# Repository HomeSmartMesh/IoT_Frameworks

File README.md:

# [website with overview, tutorials, mind maps,...](https://www.homesmartmesh.com/)

# [More recent github for Raspberry Pi scripts and nRF52](https://github.com/nRFMesh/nRF52_Mesh)

# Status
This repo is no longer in active maintenance, its main topics are :
* raspberry pi scripts and services, moved to the [nRF52](https://github.com/nRFMesh/nRF52_Mesh) repo
* microcontrolled based firmware
  * Low power STM8 replaced by off the shelf nRF51 and custom [nRF52](https://github.com/nRFMesh/nRF52_Mesh)
  * Power connected STM32 replaced by [ESP32_iot](https://github.com/HomeSmartMesh/esp32_iot)

# Hardware
### Wireless Sensor Tag
  * HW: [STM8 IoT Boards](https://github.com/HomeSmartMesh/STM8_IoT_Boards)
  * Firmware: [IoT STM8 ](https://github.com/HomeSmartMesh/IoT_STM8/tree/master/firmware_rf_sensors_node)
  * 8 bit Ultra low power & ultralow cost STM8L
  * BME280 (Pressure, Temperature, Humidity), MAX44009 (Ambient Light) and Magnetic switches
  * Custom RF protocol for efficiency and simplicity of the sensors usecase

### STM32 IoT Dongle
  * based on the STM32 bluepill
  * HW: Breadboard for easier RF and sensors modules integration [STM32 IoT Boards](https://github.com/wassfila/STM32_IoT_Boards)
  * Firmware: [stm32_rf_dongle subdirectory](https://github.com/HomeSmartMesh/IoT_Frameworks/tree/master/stm32_rf_dongle)
  * RF Mesh repeater: (decrement time to live, recalculate new CRC)
  * Light intensity, color sensor, proximity and gesture (APDS9960)
  * RGB status (WS2812B)

# Software running on the Raspberry pi

### C++ RF Gateway
[submodule rf_gateway](https://github.com/HomeSmartMesh/rf_gateway)
- Serial port line buffer
- Line parsing and sensor data extraction
- Adjustment of BME280 measures with provided calibration
- Publishing to the MQTT broquer

### Python Database proxies
scripts in the [submodule py_db_proxy](https://github.com/HomeSmartMesh/py_db_proxy)
- influx client
- mongo client
- json config and loggging

### React D3js webapp
[submodule web_react](https://github.com/HomeSmartMesh/web_react)
current status :
* automatic nodes config retriaval 
* automatic dashboard construction (but still in text mode)
* d3js still in a separate project, options beeing evaluated (nvd3 and vegas)

### Configuration
Configuration for the following software is available in the [config subdirectory](https://github.com/HomeSmartMesh/IoT_Frameworks/tree/master/config)

 * Mosquitto : MQTT Broquer
 * OpenHAB2 : used only for Wemo switch and other connected devices
 * Node-red : High level sensor to action configuration
 * Influxdb : time series database
 * Mongodb : complex documents database
 * Grafana : dashboard for measurements exploration
 * React+d3js : customised webapp

## Startup Launch on the Raspberry pi
to enable once
```
sudo systemctl enable openhab2
sudo systemctl enable influxdb
```

Others require manual startup added in
```
sudo nano /etc/rc.local
```
Debugging the rc.local log with adding the following lines
```
exec 2> /home/pi/share/rc.local.log   # send stderr from rc.local to a log file
exec 1>&2                             # send stdout to the same log file
set -x                                # tell sh to display commands before execution
```

```bash
#grafana
sudo systemctl start grafana-server.service
#iot_db
/home/pi/IoT_Frameworks/raspi_mesh_server/iot_db/iot_db &
#rf_gateway
sleep 2 && /home/pi/IoT_Frameworks/raspi_mesh_server/rf_gateway/gateway &
#mongodb : for some reason, mongodb service do not attempt reconnection on startup, but works when started a bit later
sleep 15 && sudo systemctl start mongodb.service
#mqtt_mongo
sleep 5 && python /home/pi/IoT_Frameworks/raspi_mesh_server/py_db_proxy/mqtt_mongo.py &
sleep 1 && python /home/pi/IoT_Frameworks/raspi_mesh_server/py_net_gateway/wemo_client.py &
sleep 5 && python /home/pi/IoT_Frameworks/raspi_mesh_server/py_net_gateway/milight_gateway.py &

```

Another example

```
/home/pi/IoT_Frameworks/raspi_mesh_server/rf_gateway/gateway &

python /home/pi/IoT_Frameworks/raspi_mesh_server/py_net_gateway/wemo_client.py &

python /home/pi/IoT_Frameworks/raspi_mesh_server/py_net_gateway/milight_gateway.py &

python /home/pi/IoT_Frameworks/raspi_mesh_server/ruler/ruler.py &

python /home/pi/IoT_Frameworks/raspi_mesh_server/py_net_gateway/raspi_status.py &

sleep 15 && python /home/pi/IoT_Frameworks/raspi_mesh_server/py_db_proxy/influx_client.py &
```

### Protocol helper
0x05 : Alive
0x07 : light
0x0A : bme280

0x06 : 6 - Living room
0x0F : 15- Workplace
0x1A : 26- Sleeping room
0x1D : 29
0x26 : 38- Rep test

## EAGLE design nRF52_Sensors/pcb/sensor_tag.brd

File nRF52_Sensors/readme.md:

# nRF52 Sensor Tag
* Soc : nRF52832 QF AA
* BME280
* APDS9960

# Board PIO connections
* SCL       : P0_29
* SDA       : P0_30
* APDS_Int  : P0_31
* UART_Tx   : P0_06

# Prerequisites
* GNU Tools ARM Embedded version : 6 2017-q2-update

# Included dependencies
* nRF SDK 15.0.0_a53641a linked as a submodule and stripped down to the required content
* nRF SDK size reduced to ~ 2.8 MB instead of the original 693 MB and can thus easily be treated as an always loaded submodule

# uart
* main.c        : uart_init() -> APP_UART_FIFO_INIT(), app_uart_put(), app_uart_get()
* app_uart.h    : APP_UART_FIFO_INIT() -> app_uart_init()
* app_uart.c    : app_uart_init() -> nrf_drv_uart_init() "legacy\nrf_drv_uart.c"
* nrf_serial.c  : nrf_serial_init(),nrf_serial_write(),nrf_serial_read()
                  nrf_serial_init() -> nrf_drv_uart_init() "legacy\nrf_drv_uart.c"

# nrf logger module
* http://infocenter.nordicsemi.com/index.jsp?topic=%2Fcom.nordic.infocenter.sdk5.v15.0.0%2Fgroup__nrf__log.html&cp=4_0_0_6_11_16
## sdk config
* NRF_LOG + NRF_LOG_BACKEND_UART_XXX
* NRFX_UARTE_ENABLED 1, NRFX_UARTE0_ENABLED 0
* NRFX_UART_ENABLED 1, NRFX_UART0_ENABLED 0
* UART_ENABLED 1
* NRFX_PRS_ENABLED 1, NRFX_PRS_BOX_4_ENABLED 1
## user macros
* NRF_LOG_INSTANCE_REGISTER()
* NRF_LOG_INFO("Hi\r\n");   
* NRF_LOG_FLUSH(); must be called if not deferred
* timestamp only when using app_timer.h

# Tools

## Python jlink wrapper
* https://github.com/square/pylink
* http://pylink.readthedocs.io/en/latest/pylink.html
* have to be used with a 32 bit python version

## sdk_config GUI
```make conf```
* http://helmpcb.com/software/cmsis-configuration-wizard

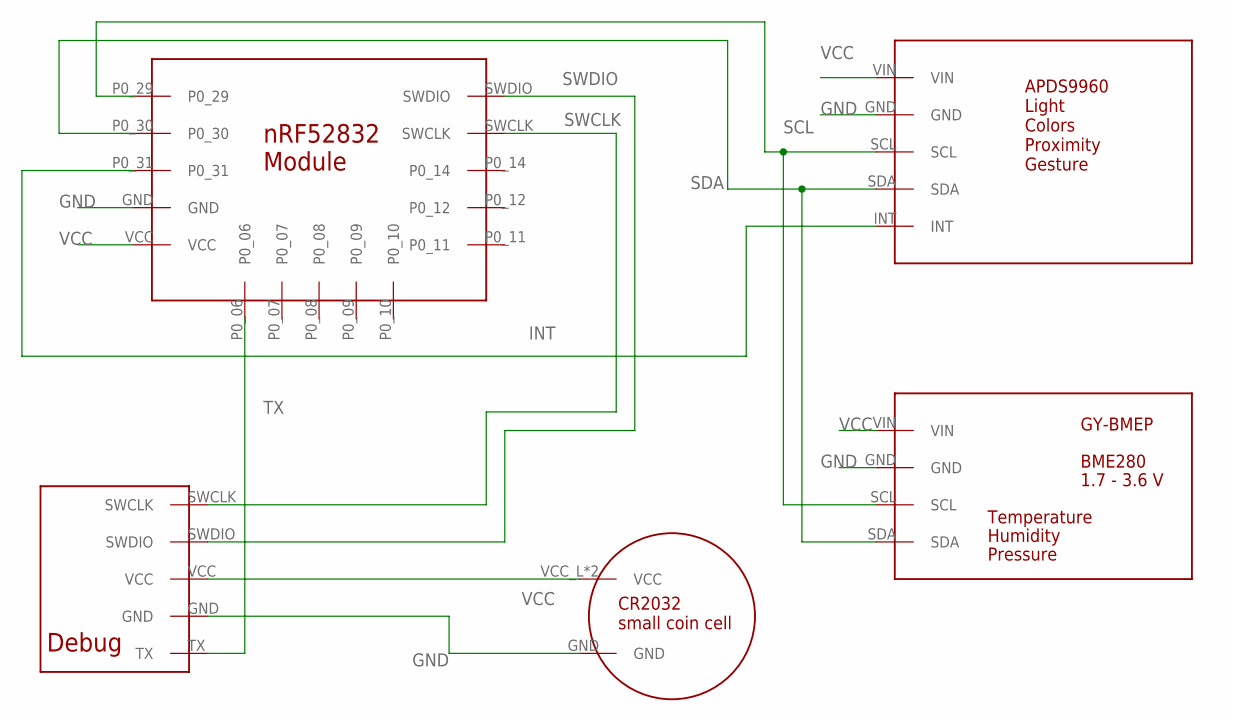
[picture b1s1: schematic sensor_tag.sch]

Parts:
U$1: GY-BMEPGY-BMEP-NOHOLE; GY-BMEP-NOHOLE
U$2: APDS9960_MODULEAPDS9960-FULL; APDS9960-FULL
U$3: NRF52832_MODULENRF52832_MOD_SMALL; NRF52832_MOD_SMALL
U$4: CR2032; CR2032_SMD
U$5: NRF_TAG_DEBUG

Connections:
GND: U$1.GND, U$2.GND, U$3.GND, U$4.GND, U$5.GND
INT: U$2.INT, U$3.P0_31
SCL: U$1.SCL, U$2.SCL, U$3.P0_29
SDA: U$1.SDA, U$2.SDA, U$3.P0_30
SWCLK: U$3.SWCLK, U$5.SWCLK
SWDIO: U$3.SWDIO, U$5.SWDIO
TX: U$3.P0_06, U$5.TX
VCC: U$1.VIN, U$2.VIN, U$3.VCC, U$4.VCC_L (VCC), U$4.VCC_R (VCC), U$5.VCC

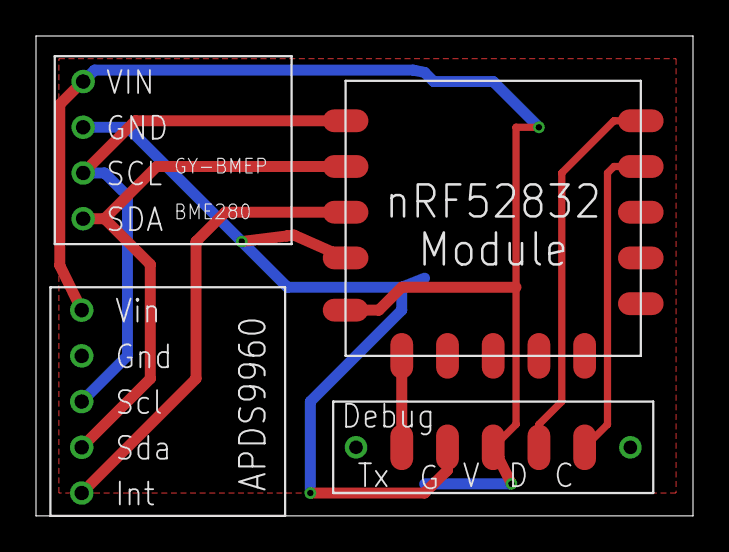
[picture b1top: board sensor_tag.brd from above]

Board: 2 copper layers, 36.5 x 26.7 mm, 5 parts (1 on the bottom side), 8 nets.

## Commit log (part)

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2017-01-06 all json cpp,node,webclient, cpp stringify with type,
2017-01-06 added amcharts viewing, experimental
2017-01-07 just to display the cranch in a pop out
2017-01-07 group nodes, group Temp, Group Light
2017-01-07 Temperature with color scales
2017-01-14 all of the db server, nodejs server, web client updated together for a json "request" "response" with id start.
2017-01-14 used ctime, added time javascript client and cpp server check, "Duration" request
2017-01-14 debug with less content on nodejs server, fix Duration dump() as "Duration", avoid empty response, date starts from 1900 then use text
2017-01-15 refined protocol for request response and update with right date-time format and json structures
2017-01-15 Added last day example with test moving line
2017-01-21 avoid sending null frame
2017-01-21 First version of the cpp sensors server that is port from the serial port logger and now includes a websocket server based on Poco
2017-01-21 issue of 9 bytes in stand of 8 helped find a segmentation fault fixed also on server side
2017-01-21 Fixed segmentation fault, yes that really could happen, hex to data conversion is now safe, streamer protected from non loaded calib files, reduced main loop, added main license, added Server Broadca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
2017-01-22 HTTP Post notification enabled with config, and another configfile for testing POST as a webserver, see test log, webserver starts conditionnaly on config,
2017-01-22 on request, sends uddate of all last values of all nodes, sensors, the update response is not sent, rather a simple 'update' is sent
2017-01-28 class used
2017-01-28 serial logger log file cleaning, handling request parameters verification
2017-01-28 refactoring timechat in a list
2017-01-29 Fixed issue #24 by checking the availability of map members before using them
2017-01-29 refactoring charts to have simple config table for params and requests
2017-01-29 removed media, all goes to repo\media
2017-01-29 change media path
2017-02-04 updated the Alive program to use common libs, and added UART disable flag
2017-02-04 new Node calib
2017-02-05 update uart config and node HW flags
2017-02-05 removed rpi_app_uart_logger to avoid confusion as it duplicates the cpp_server, updated the cpp_server config with one more node calib
2017-02-05 refactoring rf log messages to standard format, RF Bridge LED notification from main, RF Logger handling retransmission Pid
2017-02-05 last lines flood filtering, string compare, vscode settings
2017-02-05 clearer date debug for issue, no samples found
2017-02-12 added "Temperature support"
2017-02-12 HTTP Post with different json format
2017-02-13 fixed blank load issue due to one hour shift of time saving that shift the month, config file no POST
2017-02-13 added feature reset RF notification
2017-02-15 Added data rate handling and set default to 250Kbps
2017-02-18 changed RF protocol to size in first byte
2017-02-18 settle to 2 Mbps data rate
2017-02-18 Retransmission protocol with configurable delay per node in EEPROM
2017-02-19 started generic pwm timer1 and timer2, failing, not working with smartio board
2017-02-19 fixed retransmit with same header update not adding a new header, and set ttl to 0 for a single level bridging network
2017-02-19 configurable UART baud rate 115200 or 9600, to check impact on safety UART tx to server
2017-02-19 general Logger for file, cout, log levels, close to std::cout usage
2017-02-19 fixed write to br2 before is very important as not working otherwise (load on br1 write)
2017-02-24 added nRF functionnalities, Address length ok, CRC Fail no reception.
2017-02-25 started a soft timer2 pwm
2017-02-25 timer2 HW pwm running with serial server
2017-02-25 Fixed bug of BME280 only node going out of power with wait transmit and power down only after transmit
2017-02-27 new sample for RGB LED with common libs
2017-03-03 added Target Node id in rgb protocol
2017-03-04 handling of rx uart commands cmd for rgb rf send color
2017-03-04 add RGB Status capability to the bridge
2017-03-04 test for sending RGB status to nodes
2017-03-04 first test with mqtt cpp client, surprisingly simple, also added the python test
2017-03-04 mqtt publishing sensors values !!!! log level issue fixed, separate logout and logfile levels
2017-03-05 added power down sleep but with issue can set delay only once, adjustments for Magnet conditions, high current drop if wrong
2017-03-05 added Light Time charts
2017-03-06 added subscription to MQTT RGB service with NodeId in Topic path and color in json packet
2017-03-11 Starting a new rf tester master client
2017-03-11 signal test and channel switch transactions
2017-03-12 still in development, not compiling, the Point to Point RF Communication
2017-03-14 single acknowledge from the newly frush was bugy protocol, diffitulties with Flags
2017-03-19 RGB neg and disable interrupts
2017-03-21 minor config
2017-03-21 Added Balcony svg
2017-03-21 simple rgb rf with retries
2017-03-25 rf messages for acknowledged rgb set
2017-03-25 receiver logger compiling
2017-03-25 Both Logger and bridge are set to the new protocol
2017-03-26 formatted rgb set feedback log
2017-03-26 logging node id and reset to new protocol
2017-03-27 mqtt ruler started for humidity status
2017-03-27 default blue
2017-04-01 update the rgb rf
2017-04-01 rf ramping all leds
2017-05-13 added pilibs as submodule
2017-05-13 Started Joystick to servo protocol for STM32
2017-05-13 update submodule
2017-05-27 moving stm8 firmware
2017-05-27 start pi cpp project for RFPIO
2017-05-27 add startup test
2017-05-27 working rasp to dongle to RFPIO
2017-10-08 smartio delay on init
2017-10-08 stm32 rf dongle receiver
2017-10-11 sniffer app for one channel
2017-10-12 irq low workaround
2017-10-12 sniffing and printf formats
2017-10-15 start of rf_heater app
2017-10-15 prepare for the heat
2017-10-15 cleaning settings from global to local
2017-10-15 heat function in heater firmware
2017-10-16 Heat bug fixed and immidiate application
2017-10-16 added heat reaction
2017-10-20 sending generic messages
2017-11-01 removing STM8, restructuring and duplicating submodule
2017-11-01 adjusting submodules path in scons
2017-11-01 split uart text and bin to be tested
2017-11-01 moved color to mesh file protocol
2017-11-04 simple pulse generation
2017-11-04 extension to 8 channles
2017-11-05 cyclic rf ping tester
2017-11-05 mesh with spi enhancements
2017-11-18 first stm32 bridge with Protcol 2.0
2017-11-18 updated to mesh protocol 2.0
2017-11-19 Updated to Mesh 2.0 and tested
2017-11-25 Revert "ignoring debug and settings"
    This reverts commit 80082b985ee6e8e11de450d818185bc2fe33a119.
2017-11-26 Flash layout for NodeId and RF channel
2017-11-26 updated to config in flash
2017-12-02 updated submodules paths
2017-12-02 update to use json config
2017-12-03 bridge release
2017-12-03 using latest mesh_config with nodes and calibs
2017-12-04 minus letters for sensors
2017-12-08 default react app
2017-12-08 websocket crash fix
2017-12-08 main config without params
2017-12-09 update submodule for request status crash
2017-12-09 working update of map
2017-12-09 first deploayment
2017-12-09 renaming text webapp
2017-12-09 new react for more advanced app
2017-12-09 flex items
2017-12-09 catching exceptions of bad requests
2017-12-09 nodes names
2017-12-09 websocket updating nodesinfo
2017-12-10 collection name and floats
2017-12-10 running no issues websocket on connect
2017-12-10 update submodule for json to mongodb
2017-12-12 added nodes and rename
2017-12-12 added react submodule
2017-12-13 added rf gateway submodule
2017-12-13 added iot_db as a submodule
2017-12-13 update cpp gateway
2017-12-13 running gateway compiling db
2017-12-13 submodule tested
2017-12-13 restructure added py db proxy moved mqtt ruler
2017-12-14 fix db load
2017-12-14 added python ruler submodule
2017-12-14 submodule RF Raw
2017-12-15 dimmer mesh 2.0 and auto switchon light
2017-12-15 pio firmware fix rf spi module
2017-12-15 config flash still under test
2017-12-15 fixing last spi byte
2017-12-15 config update and merge
2017-12-15 file name bug and submodule
2017-12-16 update of submodules
2017-12-16 small log change
2017-12-16 added light rgb sensor and rgb led functions
2017-12-16 ugly mbed ignored submodule
2017-12-16 update submodules
2017-12-16 updated gesture and rgb light protocols
2017-12-16 added rgb to gateway
2017-12-17 configurable LED usage
2017-12-17 temporary filter and hardcoded rgb test
2017-12-17 submodule for proximity
2017-12-17 fixed light up sequence
2017-12-18 mqtt to milight bridge tested
2017-12-18 rgb demo
2017-12-19 milight bridge python start
2017-12-23 read me updates
2017-12-23 readme updates
2017-12-23 again
2017-12-23 documenting config of sw
2017-12-23 wemo start
2017-12-24 wemo client publishing
2017-12-24 doc of wemo client start
2017-12-25 log to debug
2017-12-25 raspi status bug top fixed
2017-12-25 cid for milight
2017-12-25 return 0 if dir not available
2017-12-25 influx connection exception
2017-12-25 bug wrong prasing of cpu load
2017-12-25 update influx server
2017-12-25 update repeaters
2017-12-25 ttl rf module
2017-12-26 one submodule less
2017-12-26 cleaned submodule
2017-12-26 rulers
2017-12-26 all up and running without exceptions
2017-12-26 ruler up and stable
2017-12-27 new nodes and bridge timing with defines
2017-12-27 more config, ttl and delegate bridbe
2017-12-27 topics update
2017-12-27 ruler and topic name
2017-12-28 started HCI
2017-12-29 hci client per host config and serial start
2018-01-01 Added workplace power
2018-01-02 progress on commands with tuples
2018-01-03 parsing rf in python
2018-01-04 added rx_functions control and prepared rf test
2018-01-06 rf test working, remote test still not
2018-01-06 handle test rf for the hci itself
2018-01-07 testing repeaters
2018-01-13 updated teh heater with newer nrf and crc
2018-01-13 support for heat
2018-01-14 heater update
2018-01-31 added BME280 with first tests
2018-02-02 own bme280 submodule
2018-02-02 humidity pressure and node_id config
2018-02-03 hum press temp 32 bits notify node id
2018-02-03 bridge regular tick sync
2018-02-03 light rgb and ping ttl
2018-02-14 channel tester example
2018-02-14 button protocol and retries adjutment
2018-02-19 buttons protocol
2018-02-19 button
2018-02-28 first beacon using the sdk as submodule
2018-02-28 added submodule for sensors with the correct name
2018-03-02 mpu id read from twi verified
2018-03-03 reading accell with mpu app
2018-03-04 restructure main and reset reason handling
2018-03-05 cyclic RF tx acceleration
2018-03-17 configurable beacon
2018-03-17 fixing the heat
2018-03-18 heat protocol fixing
2018-03-18 action IoT project added
2018-03-18 config nodes, timestamp and update lib
2018-03-26 compiling talk with partners array
2018-03-26 talk status online
2018-03-27 network talking
2018-03-28 highly interactivy with drunken speakers
2018-03-29 add nodes and test rgb colors
2018-03-29 testing fitness trackers
2018-04-04 first step integration of the BMP180 sensor
2018-04-14 debugging temp press measures
2018-04-14 bmp180 temp press success
2018-04-15 nodes config add new 4 nRF51 sensors
2018-04-22 adding commands on off
2018-04-22 updated new light protocol
2018-04-22 update bridge and nodes names
2018-04-22 change bathroom rule id
2018-04-30 nRF52 sensors tag pcb design and gerbers
2018-04-30 first compiling main with nRF52 using SDK
2018-04-30 changed default esb into HomeSmartMesh send button
2018-05-03 nRF52 tests ongoing
2018-05-05 printing test
2018-05-05 testing bme init hanging
2018-05-05 bme280 present and logging
2018-05-06 max44009 comes to the light
2018-05-06 lux reading with test
2018-05-08 automated reading and writing of config
2018-05-09 refactor into app files
2018-05-10 working app rtc events
2018-05-10 reading battery voltage from app
2018-05-12 formatting read and send to mesh
2018-05-19 new bat and bme protocol
2018-05-20 fixed bme280 params in uart log
2018-05-26 new node listen script and dashboards
2018-05-28 special activation key
2018-06-02 minor change save before update
2018-06-02 submodule
2018-06-03 fixed board design issues and zip gerber of new order
2018-06-03 removed submodule nRF52 SDK
2018-06-12 added rtx params
2018-06-23 updated new names and config
2018-12-21 pending changes - configurable node ids
2018-12-21 update read me
2018-12-21 refined read me
2019-10-04 nRF51802 tag temp light
